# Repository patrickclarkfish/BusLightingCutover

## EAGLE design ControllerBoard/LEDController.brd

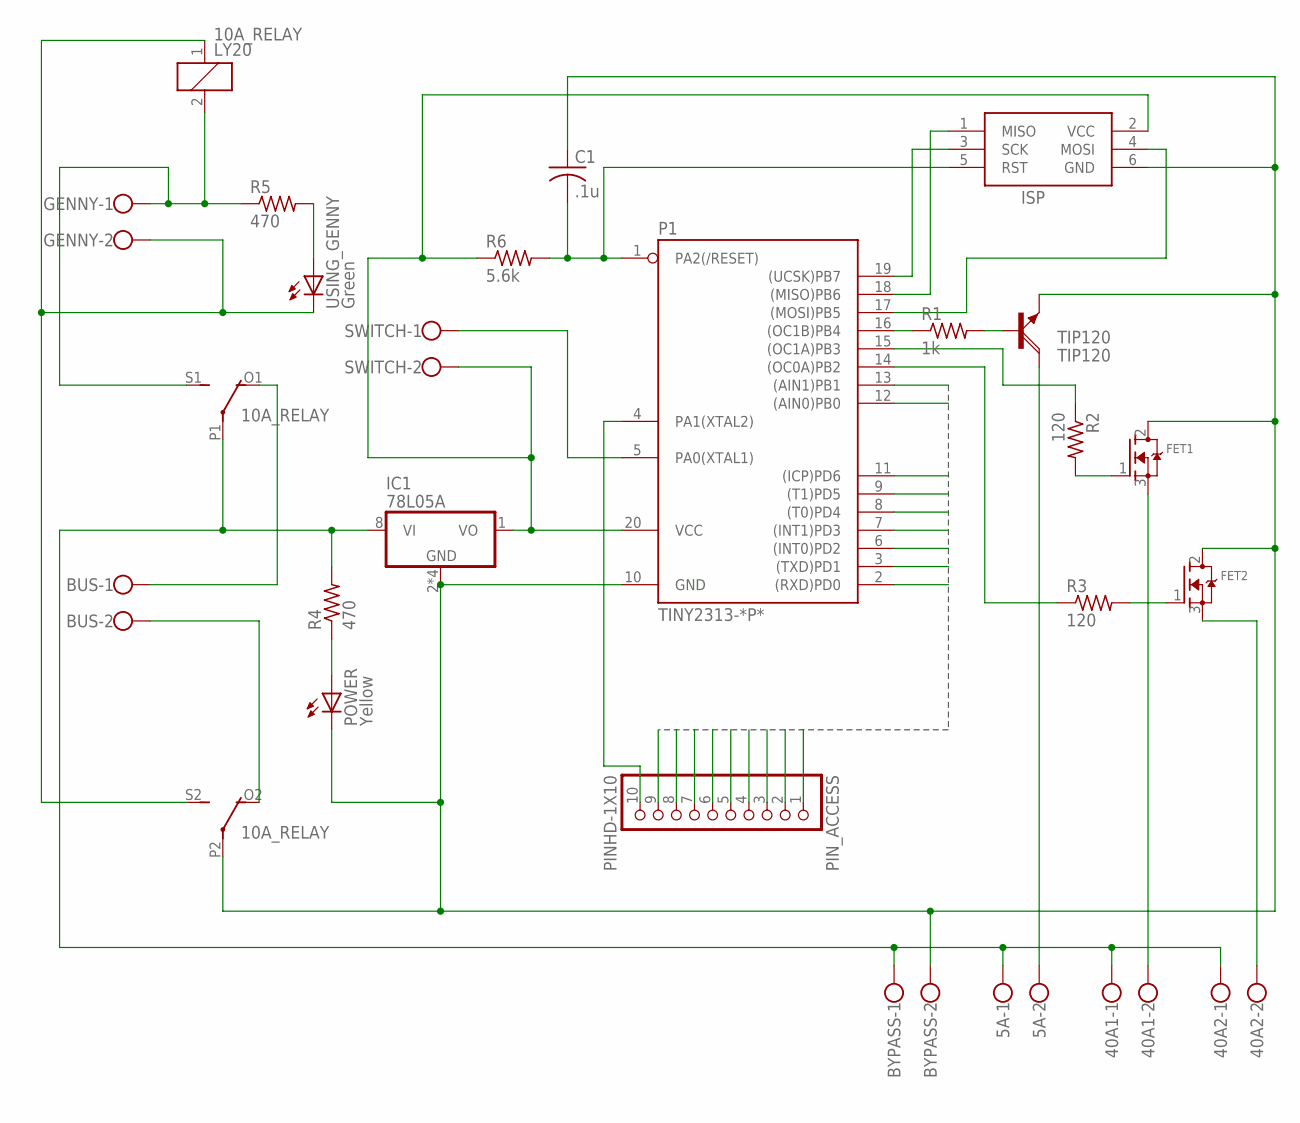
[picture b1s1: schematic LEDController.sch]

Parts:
5A, 40A1, 40A2: W237-102
10A_RELAY: LY20
BUS: W237-102
BYPASS: W237-102
C1: .1u; C025-030X050
FET1, FET2: MOSFET-NGDS_TO220V; TO220V
GENNY: W237-102
IC1: 78L05A; SOIC8
ISP: AVRISP-6; AVRISP
P1: TINY2313-*P*; DIL20
PIN_ACCESS: PINHD-1X10; 1X10-BIG
POWER: Yellow; LED5MM
R1: 1k; 0204/7
R2, R3: 120; 0204/7
R4, R5: 470; 0204/7
R6: 5.6k; 0204/7
SWITCH: W237-102
TIP120: TIP120; TO220AH
USING_GENNY: Green; LED5MM

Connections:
10A_RELAY: 10A_RELAY.1, 10A_RELAY.S2 (S), GENNY.2, USING_GENNY.K (C)
GND: 10A_RELAY.P2, BYPASS.2, C1.1, FET1.2 (D), FET2.2 (D), IC1.2 (GND), IC1.3 (GND), IC1.6 (GND), IC1.7 (GND), ISP.6 (GND), P1.10 (GND), POWER.K (C), TIP120.E
unnamed: ISP.1 (MISO), P1.18 ((MISO)PB6)
unnamed: P1.5 (PA0(XTAL1)), SWITCH.1
unnamed: P1.16 ((OC1B)PB4), R1.1
unnamed: R1.2, TIP120.B
unnamed: P1.15 ((OC1A)PB3), R2.1
unnamed: FET1.1 (G), R2.2
unnamed: P1.14 ((OC0A)PB2), R3.1
unnamed: FET2.1 (G), R3.2
unnamed: 5A.1, 10A_RELAY.P1, 40A1.1, 40A2.1, BYPASS.1, IC1.8 (VI), R4.2
unnamed: POWER.A, R4.1
unnamed: ISP.4 (MOSI), P1.17 ((MOSI)PB5)
unnamed: 10A_RELAY.2, 10A_RELAY.S1 (S), GENNY.1, R5.1
unnamed: R5.2, USING_GENNY.A
unnamed: 10A_RELAY.O1 (O), BUS.1
unnamed: 40A1.2, FET1.3 (S)
unnamed: 10A_RELAY.O2 (O), BUS.2
unnamed: 5A.2, TIP120.C
unnamed: C1.2, ISP.5 (RST), P1.1 (PA2(/RESET)), R6.2
unnamed: 40A2.2, FET2.3 (S)
unnamed: ISP.3 (SCK), P1.19 ((UCSK)PB7)
unnamed: P1.4 (PA1(XTAL2)), PIN_ACCESS.10
PIN1: P1.2 ((RXD)PD0), PIN_ACCESS.1
PIN2: P1.3 ((TXD)PD1), PIN_ACCESS.2
PIN3: P1.12 ((AIN0)PB0), PIN_ACCESS.3
PIN4: P1.13 ((AIN1)PB1), PIN_ACCESS.4
PIN5: P1.6 ((INT0)PD2), PIN_ACCESS.5
PIN6: P1.7 ((INT1)PD3), PIN_ACCESS.6
PIN7: P1.8 ((T0)PD4), PIN_ACCESS.7
PIN8: P1.9 ((T1)PD5), PIN_ACCESS.8
PIN9: P1.11 ((ICP)PD6), PIN_ACCESS.9
VCC: IC1.1 (VO), ISP.2 (VCC), P1.20 (VCC), R6.1, SWITCH.2

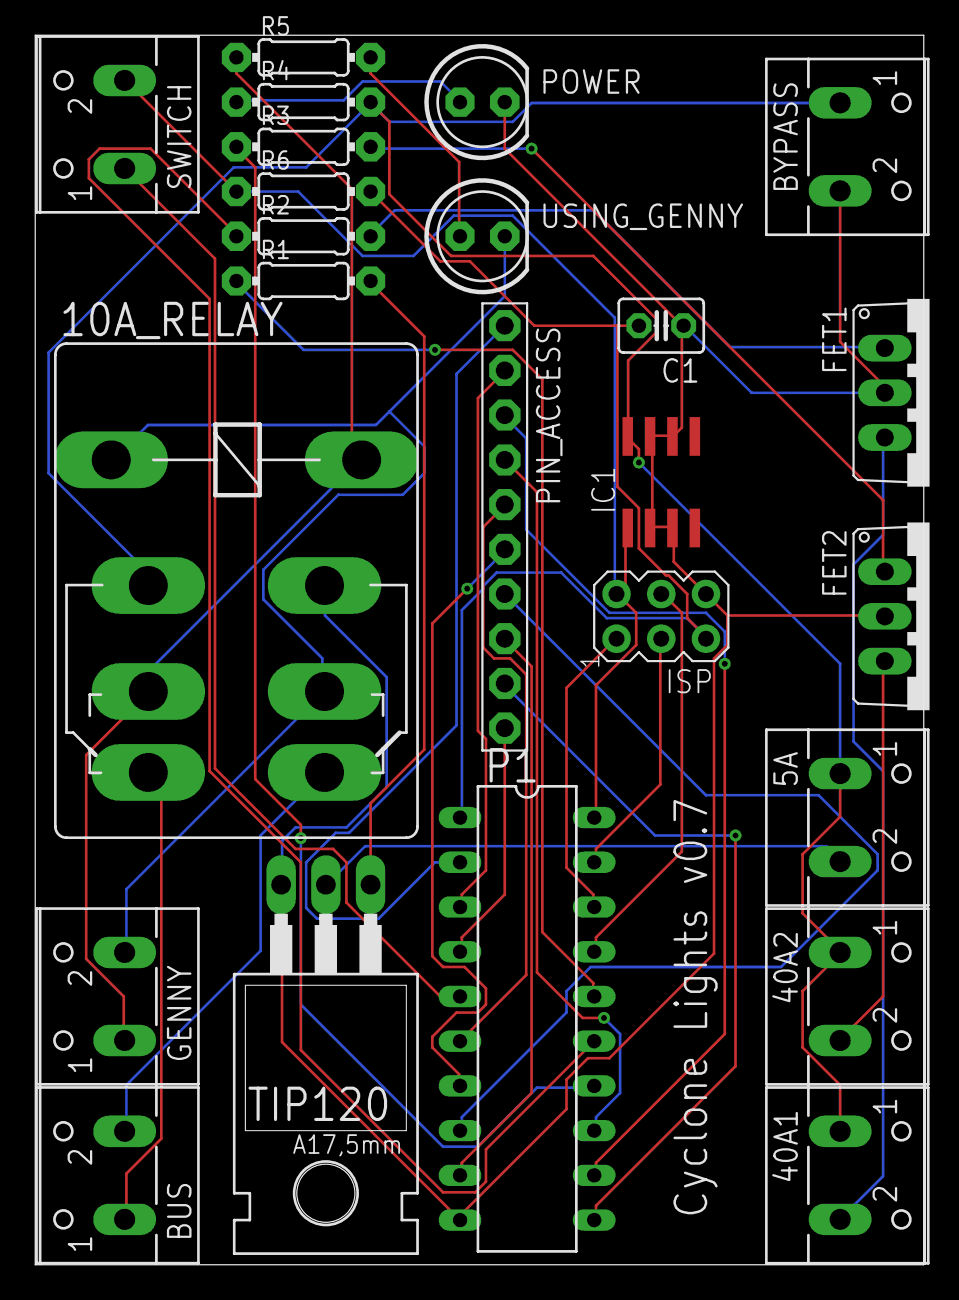
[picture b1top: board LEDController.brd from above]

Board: 2 copper layers, 50.5 x 69.8 mm, 24 parts (0 on the bottom side), 33 nets.

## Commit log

2014-08-27 :lollipop: Added .gitattributes & .gitignore files
2014-08-28 Began Implementing lighting controller
2014-08-28 added size to save/load to simplify data load.
2014-08-29 Updated Save and Load
    Still need to define details for controller a bit more.
    Added Readme
2014-08-29 Moved readme to correct folder.
2014-08-29 Added Eagle board files.
2014-08-29 Added some of the switching.
2014-09-15 update to support on/off until board is fixed.
    changes extend lighting controller functionality and make a simple main
    function to run one mosfet for now.

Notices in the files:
ControllerBoard/LEDController.brd:
(c) 2014
